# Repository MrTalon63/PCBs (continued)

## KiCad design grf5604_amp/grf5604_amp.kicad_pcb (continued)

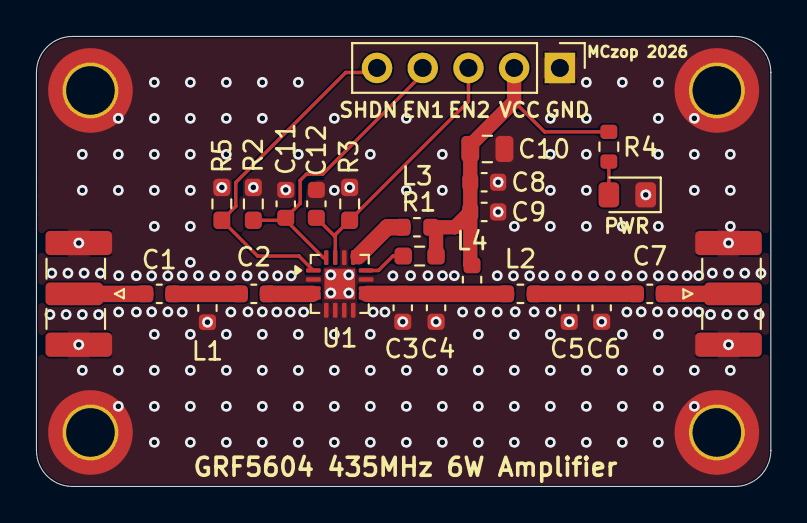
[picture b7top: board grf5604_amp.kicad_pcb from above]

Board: 2 copper layers, 40.8 x 25.0 mm, 30 parts (0 on the bottom side), 14 nets.

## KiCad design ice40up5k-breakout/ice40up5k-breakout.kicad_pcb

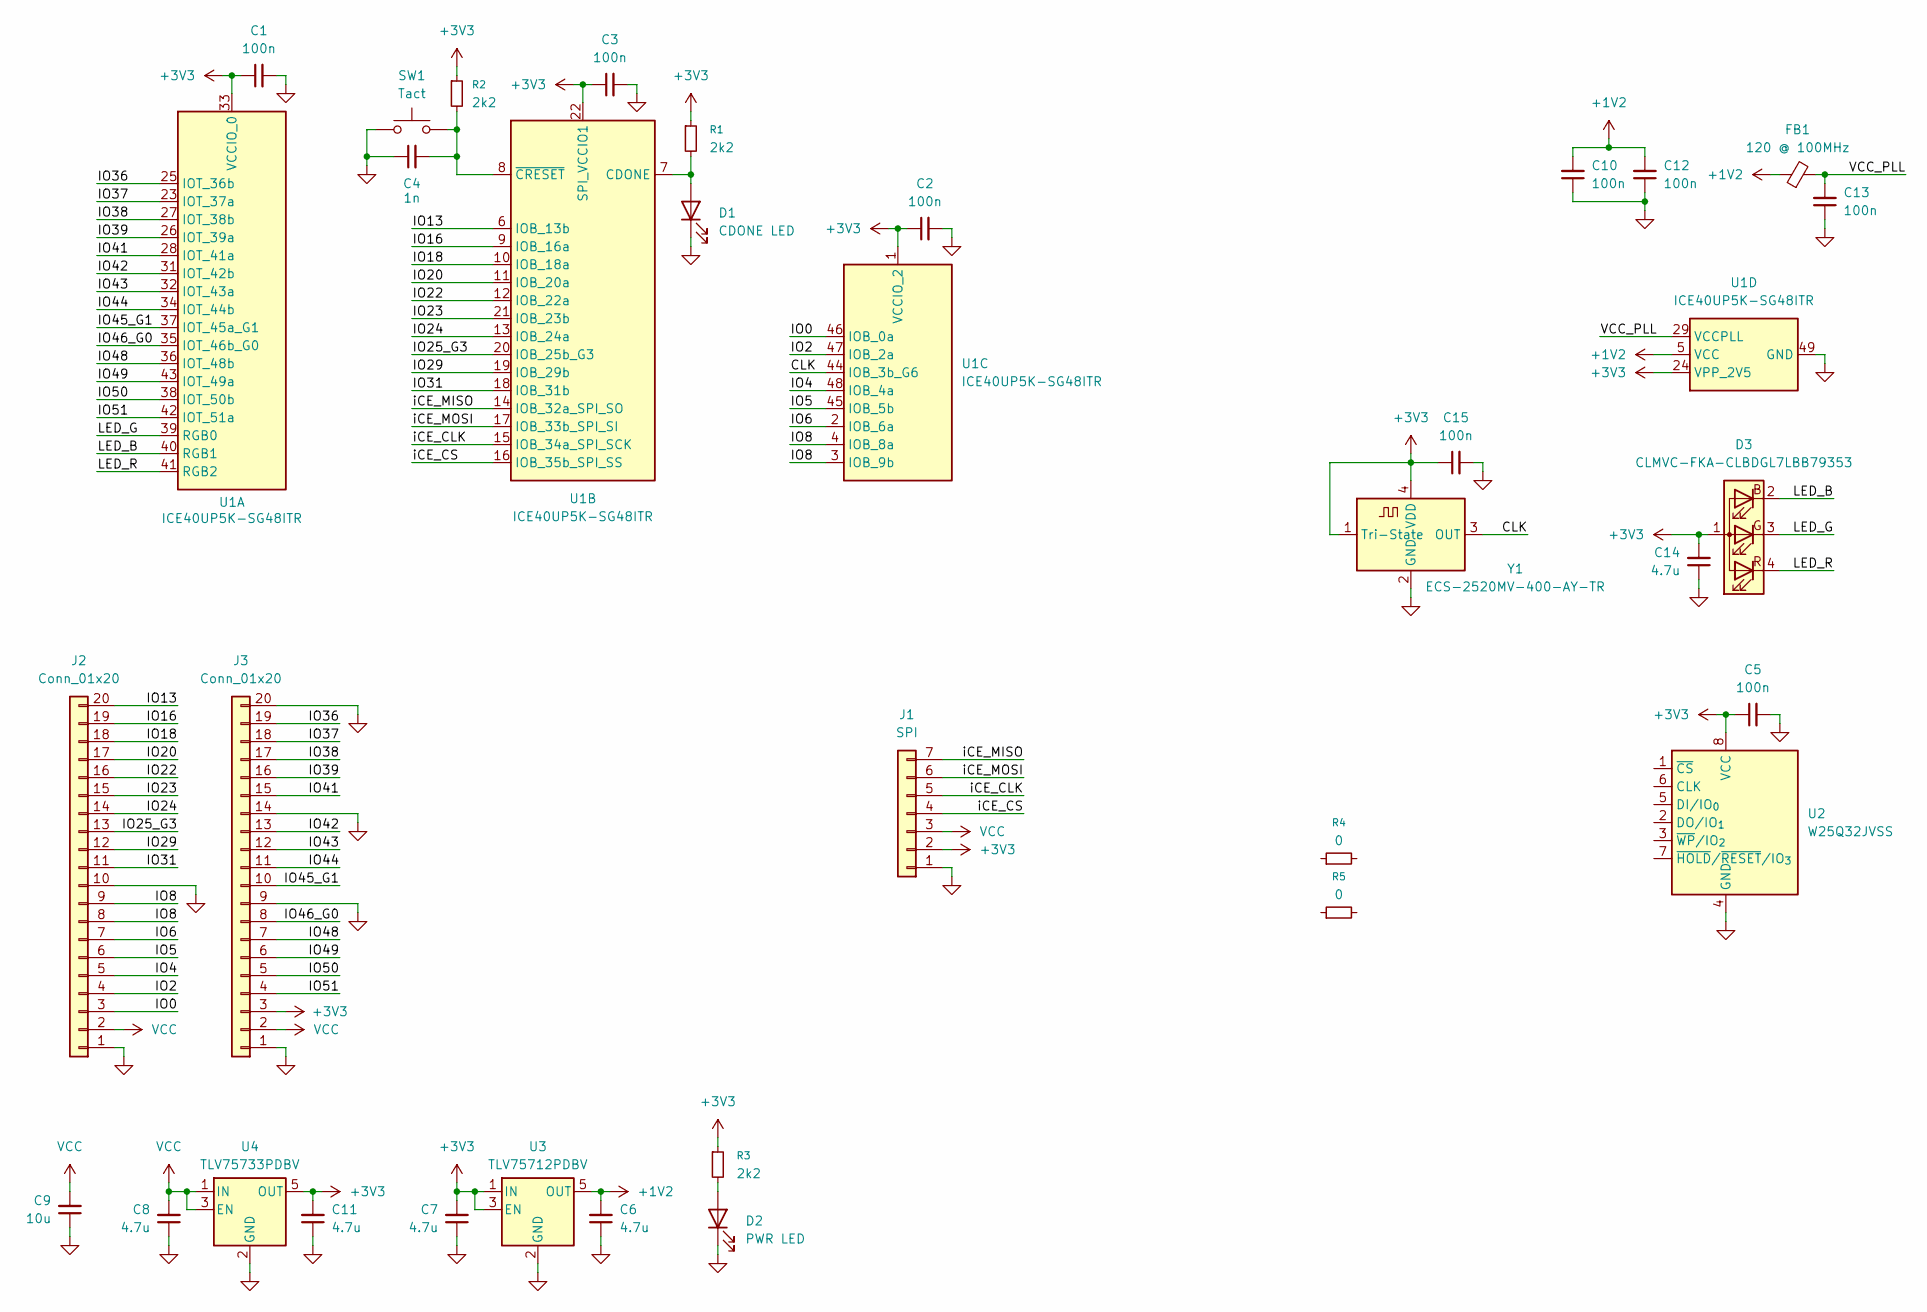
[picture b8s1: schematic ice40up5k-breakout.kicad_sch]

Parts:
C1, C2, C3, C5, C10, C12, C13, C15: 100n; C_0603_1608Metric
C4: 1n; C_0603_1608Metric
C6, C7, C8, C11, C14: 4.7u; C_0603_1608Metric
C9: 10u; C_0805_2012Metric
D1: CDONE LED; LED_0805_2012Metric
D2: PWR LED; LED_0805_2012Metric
D3: CLMVC-FKA-CLBDGL7LBB79353; LED_Cree-PLCC4_2x2mm_CW
FB1: 120 @ 100MHz; L_0603_1608Metric
J1: SPI; PinHeader_1x07_P2.54mm_Vertical
J2, J3: Conn_01x20; PinSocket_1x20_P2.54mm_Vertical
R1, R2, R3: 2k2; R_0603_1608Metric
R4, R5: 0; R_0603_1608Metric
SW1: Tact; Push_SMD_5.2x5.2mm_h1.9mm
U1: ICE40UP5K-SG48ITR; QFN-48-1EP_7x7mm_P0.5mm_EP5.6x5.6mm
U2: W25Q32JVSS; SOIC-8_5.3x5.3mm_P1.27mm
U3: TLV75712PDBV; SOT-23-5
U4: TLV75733PDBV; SOT-23-5
Y1: ECS-2520MV-400-AY-TR; Oscillator_SMD_ECS_2520MV-xxx-xx-4Pin_2.5x2.0mm

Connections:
+1V2: C6.2, C10.2, C12.2, FB1.1, U1.5 (VCC), U1.30 (VCC), U3.5 (OUT)
+3V3: C1.1, C2.1, C3.1, C5.1, C7.2, C11.2, C14.2, C15.1, D3.1 (A), J1.2, J3.3, R1.1, R2.1, R3.1, U1.1 (VCCIO_2), U1.22 (SPI_VCCIO1), U1.24 (VPP_2V5), U1.33 (VCCIO_0), U2.8 (VCC), U3.1 (IN), U3.3 (EN), U4.5 (OUT), Y1.1 (Tri-State), Y1.4 (VDD)
/CLK: U1.44 (IOB_3b_G6), Y1.3 (OUT)
/IO0: J2.3, U1.46 (IOB_0a)
/IO2: J2.4, U1.47 (IOB_2a)
/IO4: J2.5, U1.48 (IOB_4a)
/IO5: J2.6, U1.45 (IOB_5b)
/IO6: J2.7, U1.2 (IOB_6a)
/IO8: J2.8, J2.9, U1.3 (IOB_9b), U1.4 (IOB_8a)
/IO13: J2.20, U1.6 (IOB_13b)
/IO16: J2.19, U1.9 (IOB_16a)
/IO18: J2.18, U1.10 (IOB_18a)
/IO20: J2.17, U1.11 (IOB_20a)
/IO22: J2.16, U1.12 (IOB_22a)
/IO23: J2.15, U1.21 (IOB_23b)
/IO24: J2.14, U1.13 (IOB_24a)
/IO25_G3: J2.13, U1.20 (IOB_25b_G3)
/IO29: J2.12, U1.19 (IOB_29b)
/IO31: J2.11, U1.18 (IOB_31b)
/IO36: J3.19, U1.25 (IOT_36b)
/IO37: J3.18, U1.23 (IOT_37a)
/IO38: J3.17, U1.27 (IOT_38b)
/IO39: J3.16, U1.26 (IOT_39a)
/IO41: J3.15, U1.28 (IOT_41a)
/IO42: J3.13, U1.31 (IOT_42b)
/IO43: J3.12, U1.32 (IOT_43a)
/IO44: J3.11, U1.34 (IOT_44b)
/IO45_G1: J3.10, U1.37 (IOT_45a_G1)
/IO46_G0: J3.8, U1.35 (IOT_46b_G0)
/IO48: J3.7, U1.36 (IOT_48b)
/IO49: J3.6, U1.43 (IOT_49a)
/IO50: J3.5, U1.38 (IOT_50b)
/IO51: J3.4, U1.42 (IOT_51a)
/LED_B: D3.2 (BK), U1.40 (RGB1)
/LED_G: D3.3 (GK), U1.39 (RGB0)
/LED_R: D3.4 (RK), U1.41 (RGB2)
/VCC_PLL: C13.2, FB1.2, U1.29 (VCCPLL)
/iCE_CLK: J1.5, U1.15 (IOB_34a_SPI_SCK)
/iCE_CS: J1.4, U1.16 (IOB_35b_SPI_SS)
/iCE_MISO: J1.7, U1.14 (IOB_32a_SPI_SO)
/iCE_MOSI: J1.6, U1.17 (IOB_33b_SPI_SI)
GND: C1.2, C2.2, C3.2, C4.1, C5.2, C6.1, C7.1, C8.1, C9.1, C10.1, C11.1, C12.1, C13.1, C14.1, C15.2, D1.1 (K), D2.1 (K), J1.1, J2.1, J2.10, J3.1, J3.9, J3.14, J3.20, SW1.1, U1.49 (GND), U2.4 (GND), U3.2 (GND), U4.2 (GND), Y1.2 (GND)
unnamed: D1.2 (A), R1.2, U1.7 (CDONE)
unnamed: D2.2 (A), R3.2
unnamed: C4.2, R2.2, SW1.2, U1.8 (~CRESET)
VCC: C8.2, C9.2, J1.3, J2.2, J3.2, U4.1 (IN), U4.3 (EN)

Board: 2 copper layers, 33 parts (0 on the bottom side), 46 nets, no tracks yet.
